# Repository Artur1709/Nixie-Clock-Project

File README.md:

# Schematic and PCB design for nixie clock designed in EAGLE

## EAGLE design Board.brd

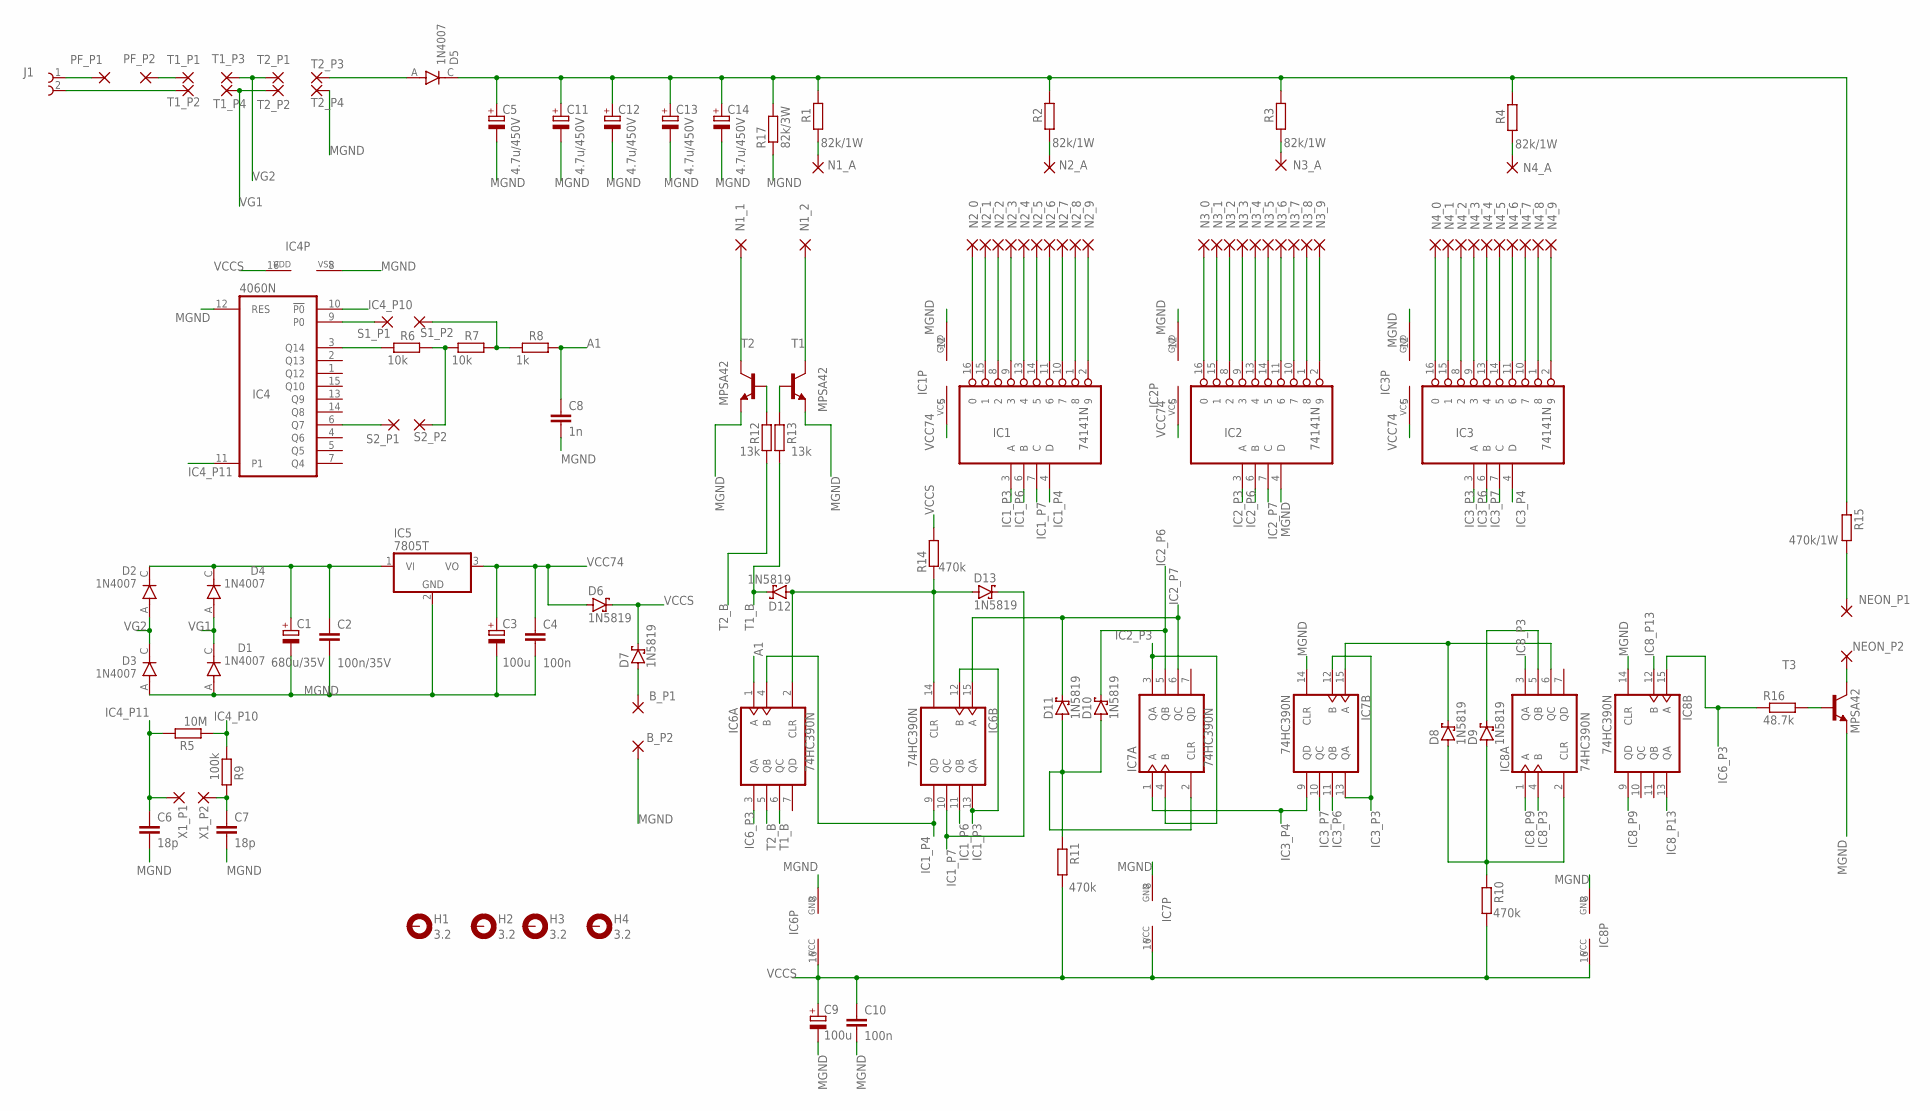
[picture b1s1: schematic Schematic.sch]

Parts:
B_P1, B_P2: 3,81/1,4
C1: 680u/35V; E5-10,5
C2: 100n/35V; C025-024X044
C3, C9: 100u; E2-4
C4, C10: 100n; C025-024X044
C5, C11, C12, C13, C14: 4.7u/450V; E5-8,5
C6, C7: 18p; C025-024X044
C8: 1n; C025-024X044
D1, D2, D3, D4, D5: 1N4007; DIOAD1060W80L520D270
D6, D7, D8, D9, D10, D11, D12, D13: 1N5819; DO41-7.6
H1, H2, H3, H4: 3.2; 3,2-PAD
IC1, IC2, IC3: 74141N; DIL16
IC4: 4060N; DIL16
IC5: 7805T; TO220H
IC6, IC7, IC8: 74HC390N; DIL16
J1: 691216910002
N1_1, N1_2, N1_A, N2_0, N2_1, N2_2, N2_3, N2_4, N2_5, N2_6, N2_7, N2_8, N2_9, N2_A, N3_0, N3_1, N3_2, N3_3, N3_4, N3_5, N3_6, N3_7, N3_8, N3_9, N3_A, N4_0, N4_1, N4_2, N4_3, N4_4, N4_5, N4_6, N4_7, N4_8, N4_9, N4_A: 3,81/1,4
NEON_P1, NEON_P2: 3,81/1,4
PF_P1, PF_P2: 3,81/1,4
R1, R2, R3, R4: 82k/1W; 0207/10
R5: 10M; 0207/10
R6, R7: 10k; 0207/10
R8: 1k; 0207/10
R9: 100k; 0207/10
R10, R11, R14: 470k; 0207/10
R12, R13: 13k; 0207/10
R15: 470k/1W; 0207/10
R16: 48.7k; 0207/10
R17: 82k/3W; 0411/12
S1_P1, S1_P2, S2_P1, S2_P2: 3,81/1,4
T1, T2, T3: MPSA42; TO92-EBC
T1_P1, T1_P2, T1_P3, T1_P4, T2_P1, T2_P2, T2_P3, T2_P4: 3,81/1,4
X1_P1, X1_P2: 1,6/0,8

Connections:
0_1: IC1.16 (0), N2_0.1
0_2: IC2.16 (0), N3_0.1
0_3: IC3.16 (0), N4_0.1
A1: C8.1, IC6.1 (A), R8.2
IC1_P3: IC1.3 (A), IC6.12 (B), IC6.13 (QA)
IC1_P4: IC1.4 (D), IC6.4 (B), IC6.9 (QD)
IC1_P6: IC1.6 (B), IC6.11 (QB)
IC1_P7: D13.C, IC1.7 (C), IC6.10 (QC)
IC2_P3: IC2.3 (A), IC7.3 (QA), IC7.4 (B)
IC2_P6: D10.C, IC2.6 (B), IC7.5 (QB)
IC2_P7: D11.C, IC2.7 (C), IC6.15 (A), IC7.6 (QC)
IC3_P3: IC3.3 (A), IC7.12 (B), IC7.13 (QA)
IC3_P4: IC3.4 (D), IC7.1 (A), IC7.9 (QD)
IC3_P6: IC3.6 (B), IC7.11 (QB)
IC3_P7: IC3.7 (C), IC7.10 (QC)
IC4_P10: IC4.10 (!P0), R5.1, R9.1
IC4_P11: C6.1, IC4.11 (P1), R5.2, X1_P1.1
IC6_P3: IC6.3 (QA), IC8.15 (A), R16.1
IC8_P3: IC8.3 (QA), IC8.4 (B)
IC8_P9: IC8.1 (A), IC8.9 (QD)
IC8_P13: IC8.12 (B), IC8.13 (QA)
MGND: B_P2.1, C1.-, C2.2, C3.-, C4.2, C5.-, C6.2, C7.2, C8.2, C9.-, C10.2, C11.-, C12.-, C13.-, C14.-, D1.A, D3.A, IC1.12 (GND), IC2.4 (D), IC2.12 (GND), IC3.12 (GND), IC4.8 (VSS), IC4.12 (RES), IC5.2 (GND), IC6.8 (GND), IC7.8 (GND), IC7.14 (CLR), IC8.8 (GND), IC8.14 (CLR), R17.1, T1.E, T2.E, T2_P4.1, T3.E
unnamed: J1.1, PF_P1.1
unnamed: J1.2, T1_P2.1
unnamed: D5.A, T2_P3.1
unnamed: C5.+, C11.+, C12.+, C13.+, C14.+, D5.C, R1.2, R2.2, R3.2, R4.2, R15.1, R17.2
unnamed: N2_A.1, R2.1
unnamed: N3_A.1, R3.1
unnamed: N4_A.1, R4.1
unnamed: N1_A.1, R1.1
unnamed: IC4.9 (P0), S1_P1.1
unnamed: IC4.6 (Q7), S2_P1.1
unnamed: IC4.3 (Q14), R6.1
unnamed: R6.2, R7.1, S2_P2.1
unnamed: R7.2, R8.1, S1_P2.1
unnamed: D12.A, D13.A, IC6.2 (CLR), IC6.14 (CLR), R14.1
unnamed: IC1.15 (1), N2_1.1
unnamed: C1.+, C2.1, D2.C, D4.C, IC5.1 (VI)
unnamed: B_P1.1, D7.A
unnamed: IC1.8 (2), N2_2.1
unnamed: IC1.9 (3), N2_3.1
unnamed: IC1.13 (4), N2_4.1
unnamed: IC1.14 (5), N2_5.1
unnamed: IC1.11 (6), N2_6.1
unnamed: IC1.10 (7), N2_7.1
unnamed: IC1.1 (8), N2_8.1
unnamed: IC1.2 (9), N2_9.1
unnamed: IC2.15 (1), N3_1.1
unnamed: IC2.8 (2), N3_2.1
unnamed: IC2.9 (3), N3_3.1
unnamed: IC2.13 (4), N3_4.1
unnamed: IC2.14 (5), N3_5.1
unnamed: IC2.11 (6), N3_6.1
unnamed: IC2.10 (7), N3_7.1
unnamed: IC2.1 (8), N3_8.1
unnamed: IC2.2 (9), N3_9.1
unnamed: IC3.15 (1), N4_1.1
unnamed: IC3.8 (2), N4_2.1
unnamed: IC3.9 (3), N4_3.1
unnamed: IC3.13 (4), N4_4.1
unnamed: IC3.14 (5), N4_5.1
unnamed: IC3.11 (6), N4_6.1
unnamed: IC3.10 (7), N4_7.1
unnamed: IC3.1 (8), N4_8.1
unnamed: IC3.2 (9), N4_9.1
unnamed: C7.1, R9.2, X1_P2.1
unnamed: R13.2, T2.B
unnamed: D8.A, D9.A, IC8.2 (CLR), R10.1
unnamed: D8.C, IC7.15 (A), IC8.6 (QC)
unnamed: D9.C, IC8.5 (QB)
unnamed: D10.A, D11.A, IC7.2 (CLR), R11.1
unnamed: N1_1.1, T1.C
unnamed: N1_2.1, T2.C
unnamed: NEON_P1.1, R15.2
unnamed: NEON_P2.1, T3.C
unnamed: R16.2, T3.B
unnamed: R12.2, T1.B
unnamed: PF_P2.1, T1_P1.1
T1_B: D12.C, IC6.6 (QC), R13.1
T2_B: IC6.5 (QB), R12.1
VCC74: C3.+, C4.1, D6.A, IC1.5 (VCC), IC2.5 (VCC), IC3.5 (VCC), IC5.3 (VO)
VCCS: C9.+, C10.1, D6.C, D7.C, IC4.16 (VDD), IC6.16 (VCC), IC7.16 (VCC), IC8.16 (VCC), R10.2, R11.2, R14.2
VG1: D1.C, D4.A, T1_P4.1, T2_P2.1
VG2: D2.A, D3.C, T1_P3.1, T2_P1.1

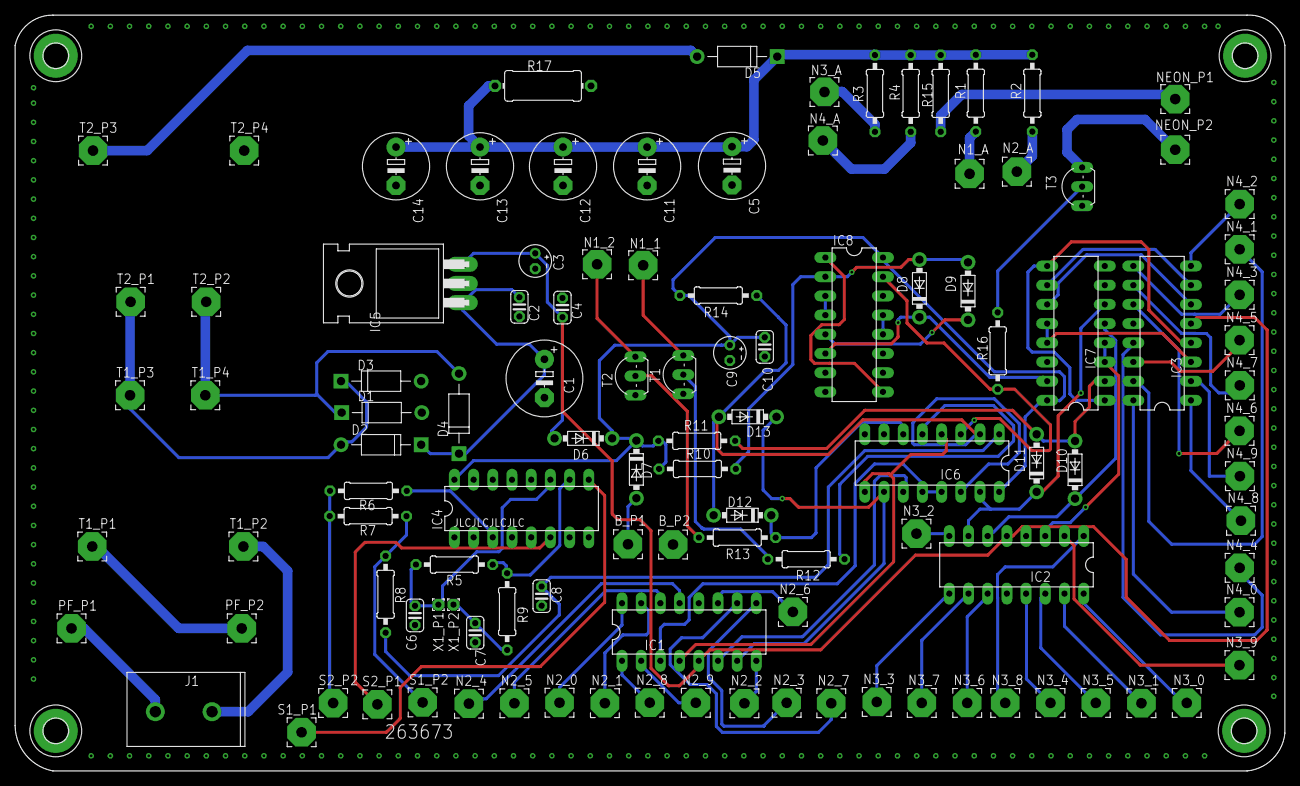
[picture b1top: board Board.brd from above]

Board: 2 copper layers, 168.0 x 100.0 mm, 116 parts (0 on the bottom side), 84 nets.

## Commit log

2024-04-22 Added Nixie Clock Files
2024-04-22 Deleted invalid files
2024-04-22 Added valid files
